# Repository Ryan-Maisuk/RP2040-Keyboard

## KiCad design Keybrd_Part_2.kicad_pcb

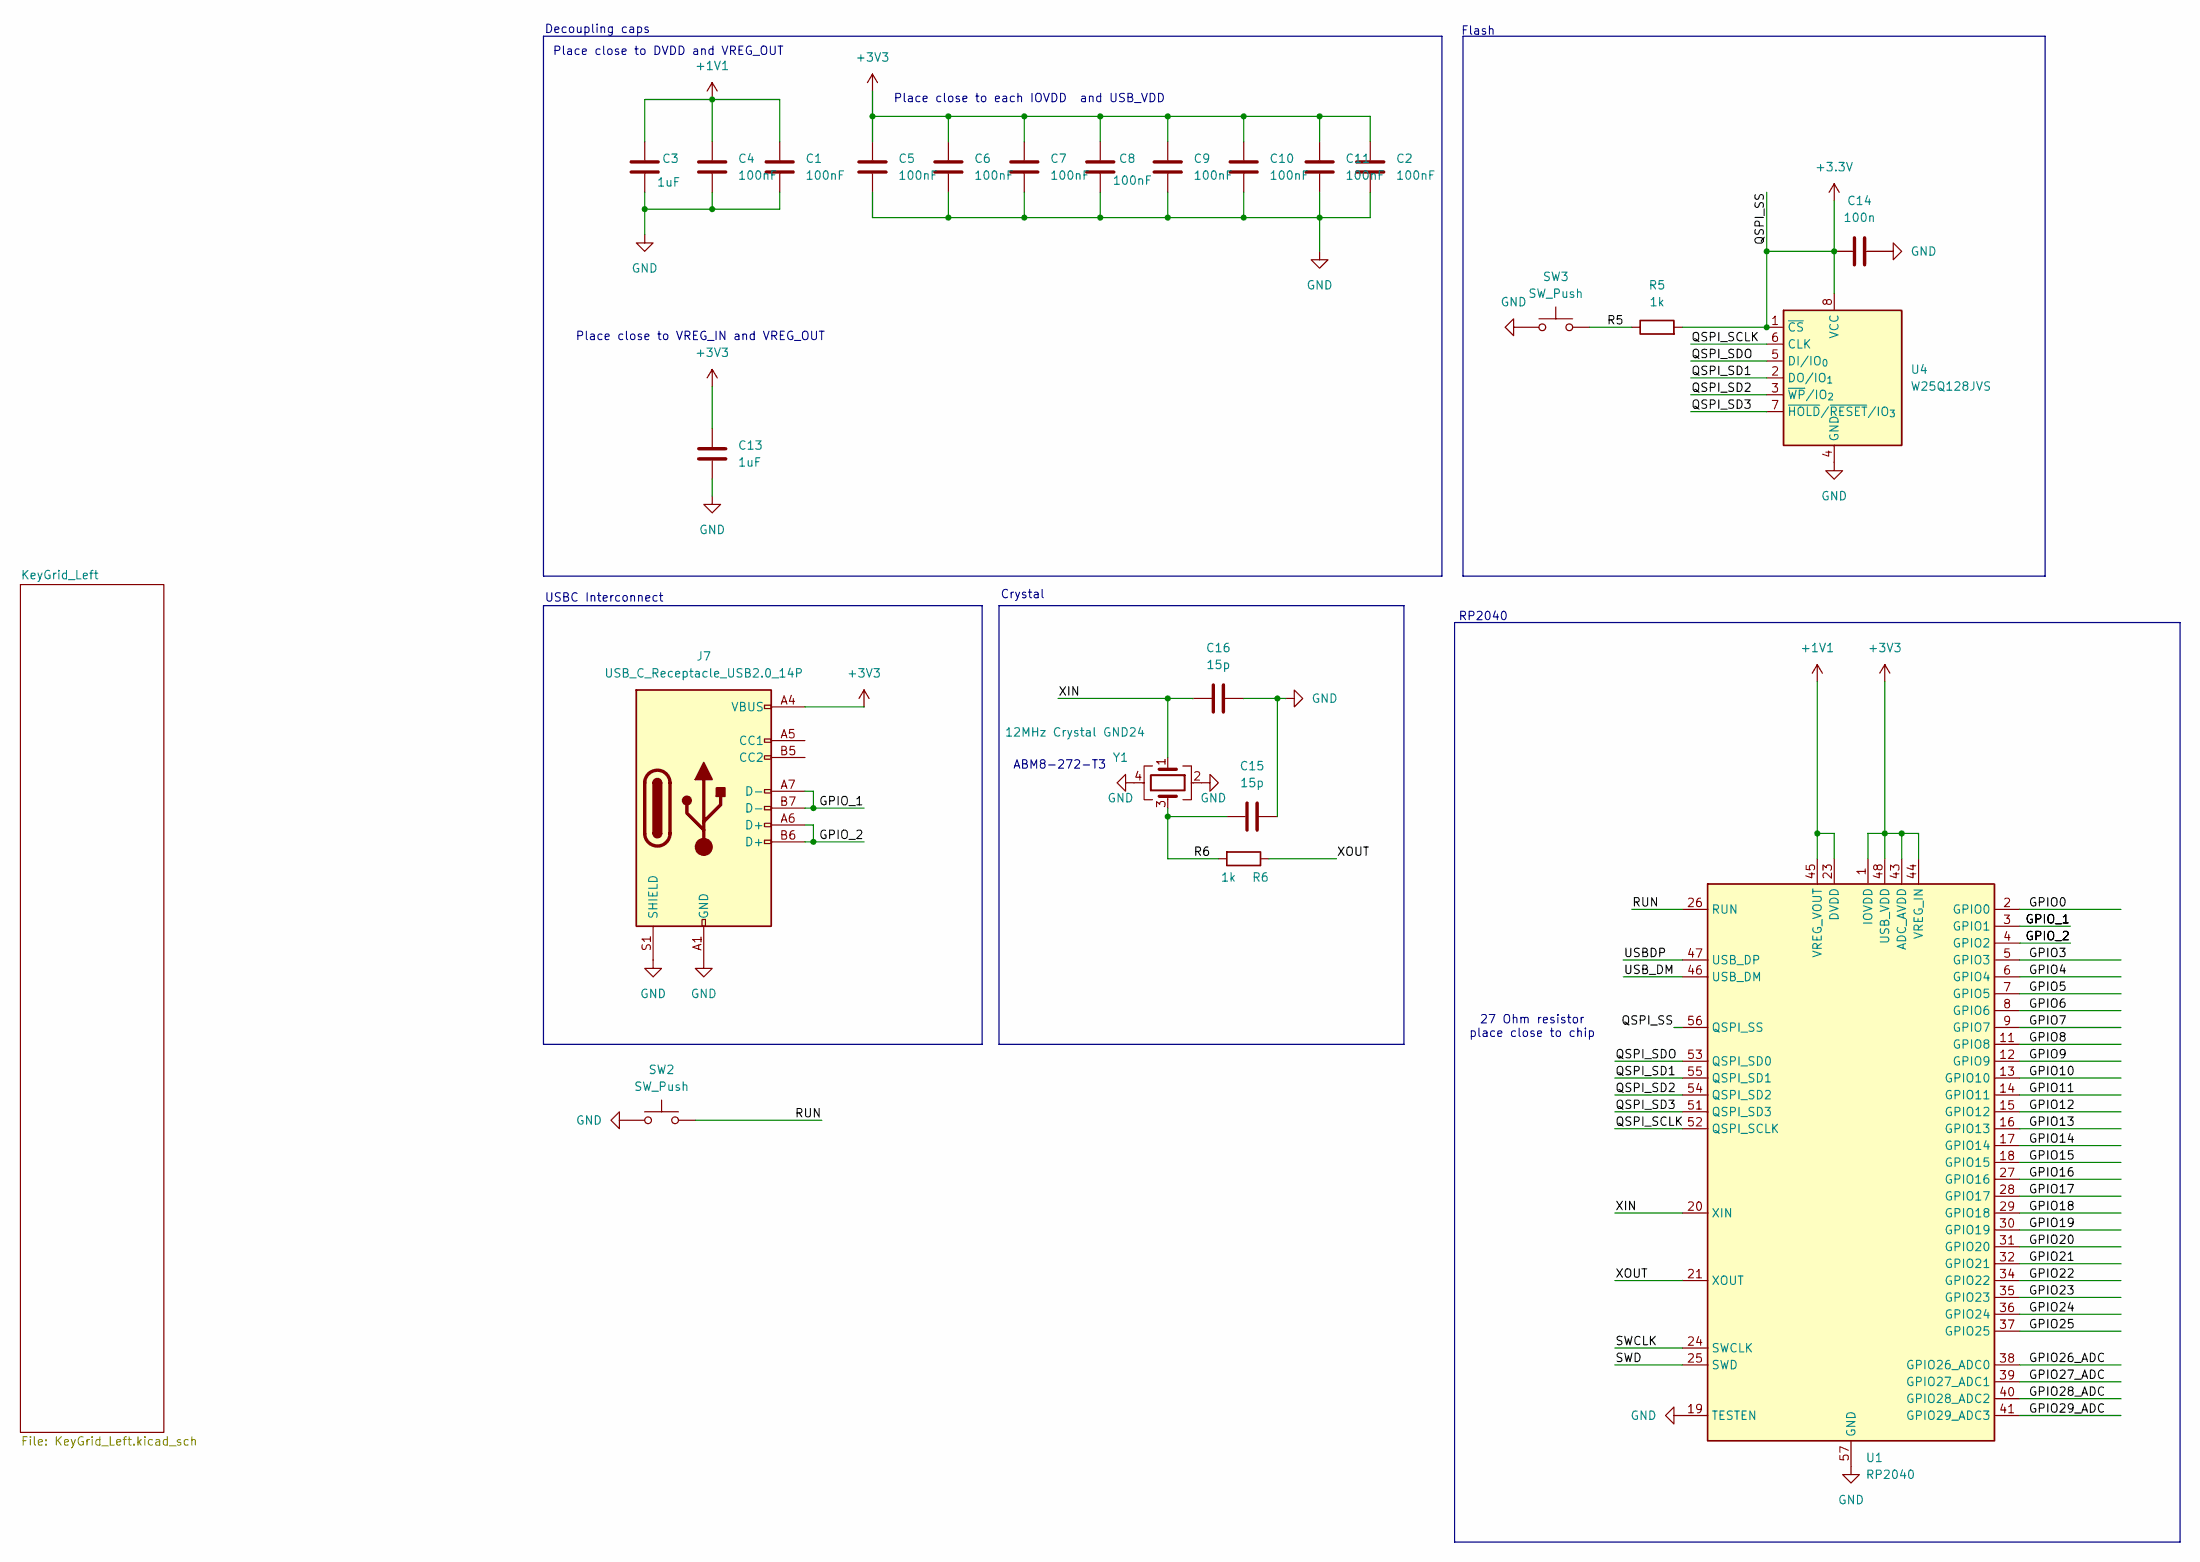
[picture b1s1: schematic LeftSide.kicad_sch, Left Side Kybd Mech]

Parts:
C1, C2, C4, C5, C6, C7, C8, C9, C10, C11: 100nF; C_0603_1608Metric_Pad1.08x0.95mm_HandSolder
C3, C13: 1uF; C_0603_1608Metric_Pad1.08x0.95mm_HandSolder
C14: 100n; C_0603_1608Metric_Pad1.08x0.95mm_HandSolder
C15, C16: 15p; C_0603_1608Metric_Pad1.08x0.95mm_HandSolder
J7: USB_C_Receptacle_USB2.0_14P; USB_C_Receptacle_Amphenol_12401548E4-2A
R5, R6: 1k; R_0603_1608Metric_Pad0.98x0.95mm_HandSolder
SW2, SW3: SW_Push; SW_PTS636_SM43J_SMTR_LFS
U1: RP2040; QFN-56-1EP_7x7mm_P0.4mm_EP3.2x3.2mm
U4: W25Q128JVS; SOIC-8_5.3x5.3mm_P1.27mm
Y1: 12MHz Crystal GND24; Crystal_SMD_3225-4Pin_3.2x2.5mm

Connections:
+1V1: C1.1, C3.1, C4.1, U1.23 (DVDD), U1.45 (VREG_VOUT), U1.50 (DVDD); also elsewhere on the board
+3.3V: C14.1, R5.2, U1.56 (QSPI_SS), U4.1 (~CS), U4.8 (VCC); also elsewhere on the board
+3V3: C2.1, C5.1, C6.1, C7.1, C8.2, C9.1, C10.1, C11.1, C13.1, J7.A4 (VBUS), J7.A9 (VBUS), J7.B4 (VBUS), J7.B9 (VBUS), U1.1 (IOVDD), U1.10 (IOVDD), U1.22 (IOVDD), U1.33 (IOVDD), U1.42 (IOVDD), U1.43 (ADC_AVDD), U1.44 (VREG_IN), U1.48 (USB_VDD), U1.49 (IOVDD); also elsewhere on the board
/LeftSide/GPIO0: U1.2 (GPIO0)
/LeftSide/GPIO3: U1.5 (GPIO3)
/LeftSide/GPIO4: U1.6 (GPIO4)
/LeftSide/GPIO5: U1.7 (GPIO5)
/LeftSide/GPIO6: U1.8 (GPIO6)
/LeftSide/GPIO7: U1.9 (GPIO7)
/LeftSide/GPIO8: U1.11 (GPIO8)
/LeftSide/GPIO9: U1.12 (GPIO9)
/LeftSide/GPIO10: U1.13 (GPIO10)
/LeftSide/GPIO11: U1.14 (GPIO11)
/LeftSide/GPIO12: U1.15 (GPIO12)
/LeftSide/GPIO13: U1.16 (GPIO13)
/LeftSide/GPIO14: U1.17 (GPIO14)
/LeftSide/GPIO15: U1.18 (GPIO15)
/LeftSide/GPIO16: U1.27 (GPIO16)
/LeftSide/GPIO17: U1.28 (GPIO17)
/LeftSide/GPIO18: U1.29 (GPIO18)
/LeftSide/GPIO19: U1.30 (GPIO19)
/LeftSide/GPIO20: U1.31 (GPIO20)
/LeftSide/GPIO21: U1.32 (GPIO21)
/LeftSide/GPIO22: U1.34 (GPIO22)
/LeftSide/GPIO23: U1.35 (GPIO23)
/LeftSide/GPIO24: U1.36 (GPIO24)
/LeftSide/GPIO25: U1.37 (GPIO25)
/LeftSide/GPIO26_ADC: U1.38 (GPIO26_ADC0)
/LeftSide/GPIO27_ADC: U1.39 (GPIO27_ADC1)
/LeftSide/GPIO28_ADC: U1.40 (GPIO28_ADC2)
/LeftSide/GPIO29_ADC: U1.41 (GPIO29_ADC3)
/LeftSide/GPIO_1: J7.A7 (D-), J7.B7 (D-), U1.3 (GPIO1)
/LeftSide/GPIO_2: J7.A6 (D+), J7.B6 (D+), U1.4 (GPIO2)
/LeftSide/QSPI_SCLK: U1.52 (QSPI_SCLK), U4.6 (CLK)
/LeftSide/QSPI_SD1: U1.55 (QSPI_SD1), U4.2 (DO/IO_{1})
/LeftSide/QSPI_SD2: U1.54 (QSPI_SD2), U4.3 (~WP/IO_{2})
/LeftSide/QSPI_SD3: U1.51 (QSPI_SD3), U4.7 (~HOLD/~RESET/IO_{3})
/LeftSide/QSPI_SDO: U1.53 (QSPI_SD0), U4.5 (DI/IO_{0})
/LeftSide/R5: R5.1, SW3.2
/LeftSide/R6: C15.1, R6.2, Y1.3
/LeftSide/RUN: SW2.2, U1.26 (RUN)
/LeftSide/SWCLK: U1.24 (SWCLK)
/LeftSide/SWD: U1.25 (SWD)
/LeftSide/USBDP: U1.47 (USB_DP)
/LeftSide/USB_DM: U1.46 (USB_DM)
/LeftSide/XIN: C16.1, U1.20 (XIN), Y1.1
/LeftSide/XOUT: R6.1, U1.21 (XOUT)
GND: C1.2, C2.2, C3.2, C4.2, C5.2, C6.2, C7.2, C8.1, C9.2, C10.2, C11.2, C13.2, C14.2, C15.2, C16.2, J7.A1 (GND), J7.A12 (GND), J7.B1 (GND), J7.B12 (GND), J7.S1 (SHIELD), SW2.1, SW3.1, U1.19 (TESTEN), U1.57 (GND), U4.4 (GND), Y1.2, Y1.4; also elsewhere on the board

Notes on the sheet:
RP2040
Place close to each IOVDD and USB_VDD
USBC Interconnect
27 Ohm resistor place close to chip
Decoupling caps
Flash
Place close to DVDD and VREG_OUT
ABM8-272-T3
Crystal
Place close to VREG_IN and VREG_OUT

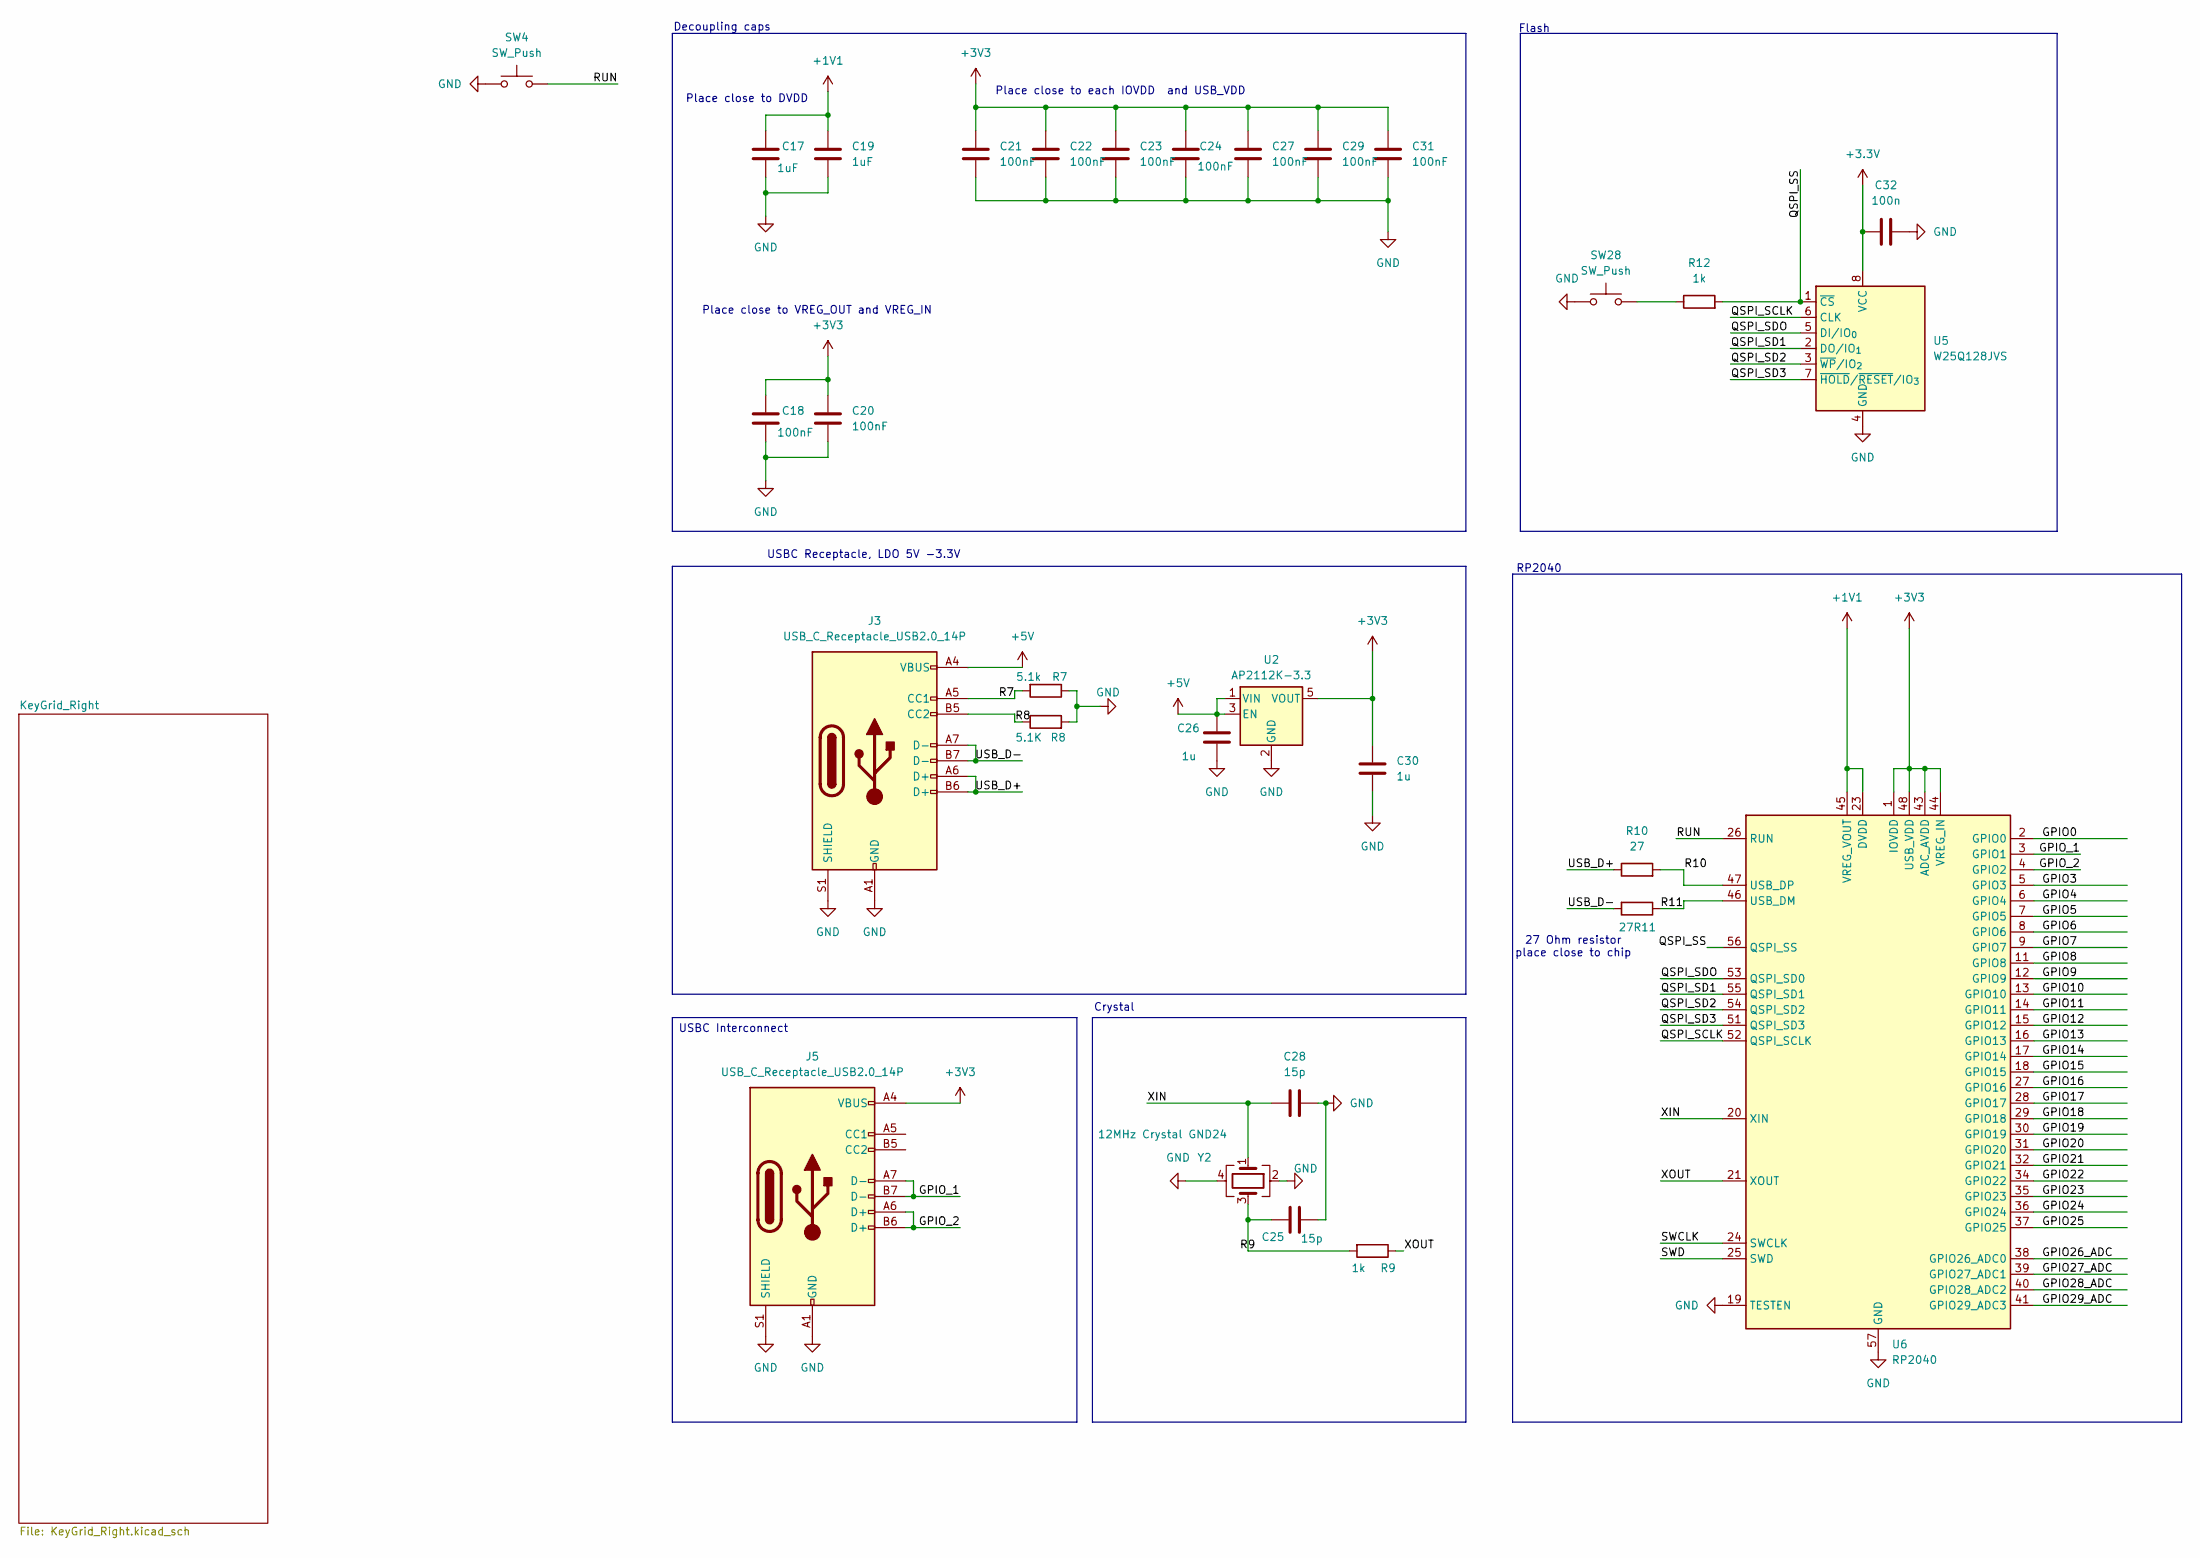
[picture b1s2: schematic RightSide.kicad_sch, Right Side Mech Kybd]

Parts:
C17, C19: 1uF; C_0603_1608Metric_Pad1.08x0.95mm_HandSolder
C18, C20, C21, C22, C23, C24, C27, C29, C31: 100nF; C_0603_1608Metric_Pad1.08x0.95mm_HandSolder
C25, C28: 15p; C_0603_1608Metric_Pad1.08x0.95mm_HandSolder
C26, C30: 1u; C_0603_1608Metric_Pad1.08x0.95mm_HandSolder
C32: 100n; C_0603_1608Metric_Pad1.08x0.95mm_HandSolder
J3, J5: USB_C_Receptacle_USB2.0_14P; USB_C_Receptacle_Amphenol_12401548E4-2A
R7: 5.1k; R_0603_1608Metric_Pad0.98x0.95mm_HandSolder
R8: 5.1K; R_0603_1608Metric_Pad0.98x0.95mm_HandSolder
R9, R12: 1k; R_0603_1608Metric_Pad0.98x0.95mm_HandSolder
R10, R11: 27; R_0603_1608Metric_Pad0.98x0.95mm_HandSolder
SW4, SW28: SW_Push; SW_PTS636_SM43J_SMTR_LFS
U2: AP2112K-3.3; SOT-23-5
U5: W25Q128JVS; SOIC-8_5.3x5.3mm_P1.27mm
U6: RP2040; QFN-56-1EP_7x7mm_P0.4mm_EP3.2x3.2mm
Y2: 12MHz Crystal GND24; Crystal_SMD_3225-4Pin_3.2x2.5mm

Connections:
+1V1: C17.1, C19.1, U6.23 (DVDD), U6.45 (VREG_VOUT), U6.50 (DVDD); also elsewhere on the board
+3.3V: C32.1, U5.8 (VCC); also elsewhere on the board
+3V3: C18.1, C20.1, C21.1, C22.1, C23.1, C24.2, C27.1, C29.1, C30.1, C31.1, J5.A4 (VBUS), J5.A9 (VBUS), J5.B4 (VBUS), J5.B9 (VBUS), U2.5 (VOUT), U6.1 (IOVDD), U6.10 (IOVDD), U6.22 (IOVDD), U6.33 (IOVDD), U6.42 (IOVDD), U6.43 (ADC_AVDD), U6.44 (VREG_IN), U6.48 (USB_VDD), U6.49 (IOVDD); also elsewhere on the board
+5V: C26.1, J3.A4 (VBUS), J3.A9 (VBUS), J3.B4 (VBUS), J3.B9 (VBUS), U2.1 (VIN), U2.3 (EN)
/RightSide/GPIO0: U6.2 (GPIO0)
/RightSide/GPIO3: U6.5 (GPIO3)
/RightSide/GPIO4: U6.6 (GPIO4)
/RightSide/GPIO5: U6.7 (GPIO5)
/RightSide/GPIO6: U6.8 (GPIO6)
/RightSide/GPIO7: U6.9 (GPIO7)
/RightSide/GPIO8: U6.11 (GPIO8)
/RightSide/GPIO9: U6.12 (GPIO9)
/RightSide/GPIO10: U6.13 (GPIO10)
/RightSide/GPIO11: U6.14 (GPIO11)
/RightSide/GPIO12: U6.15 (GPIO12)
/RightSide/GPIO13: U6.16 (GPIO13)
/RightSide/GPIO14: U6.17 (GPIO14)
/RightSide/GPIO15: U6.18 (GPIO15)
/RightSide/GPIO16: U6.27 (GPIO16)
/RightSide/GPIO17: U6.28 (GPIO17)
/RightSide/GPIO18: U6.29 (GPIO18)
/RightSide/GPIO19: U6.30 (GPIO19)
/RightSide/GPIO20: U6.31 (GPIO20)
/RightSide/GPIO21: U6.32 (GPIO21)
/RightSide/GPIO22: U6.34 (GPIO22)
/RightSide/GPIO23: U6.35 (GPIO23)
/RightSide/GPIO24: U6.36 (GPIO24)
/RightSide/GPIO25: U6.37 (GPIO25)
/RightSide/GPIO26_ADC: U6.38 (GPIO26_ADC0)
/RightSide/GPIO27_ADC: U6.39 (GPIO27_ADC1)
/RightSide/GPIO28_ADC: U6.40 (GPIO28_ADC2)
/RightSide/GPIO29_ADC: U6.41 (GPIO29_ADC3)
/RightSide/GPIO_1: J5.A7 (D-), J5.B7 (D-), U6.3 (GPIO1)
/RightSide/GPIO_2: J5.A6 (D+), J5.B6 (D+), U6.4 (GPIO2)
/RightSide/QSPI_SCLK: U5.6 (CLK), U6.52 (QSPI_SCLK)
/RightSide/QSPI_SD1: U5.2 (DO/IO_{1}), U6.55 (QSPI_SD1)
/RightSide/QSPI_SD2: U5.3 (~WP/IO_{2}), U6.54 (QSPI_SD2)
/RightSide/QSPI_SD3: U5.7 (~HOLD/~RESET/IO_{3}), U6.51 (QSPI_SD3)
/RightSide/QSPI_SDO: U5.5 (DI/IO_{0}), U6.53 (QSPI_SD0)
/RightSide/QSPI_SS: R12.2, U5.1 (~CS), U6.56 (QSPI_SS)
/RightSide/R7: J3.A5 (CC1), R7.2
/RightSide/R8: J3.B5 (CC2), R8.1
/RightSide/R9: C25.1, R9.2, Y2.3
/RightSide/R10: R10.2, U6.47 (USB_DP)
/RightSide/R11: R11.1, U6.46 (USB_DM)
/RightSide/RUN: SW4.2, U6.26 (RUN)
/RightSide/SWCLK: U6.24 (SWCLK)
/RightSide/SWD: U6.25 (SWD)
/RightSide/USB_D+: J3.A6 (D+), J3.B6 (D+), R10.1
/RightSide/USB_D-: J3.A7 (D-), J3.B7 (D-), R11.2
/RightSide/XIN: C28.1, U6.20 (XIN), Y2.1
/RightSide/XOUT: R9.1, U6.21 (XOUT)
GND: C17.2, C18.2, C19.2, C20.2, C21.2, C22.2, C23.2, C24.1, C25.2, C26.2, C27.2, C28.2, C29.2, C30.2, C31.2, C32.2, J3.A1 (GND), J3.A12 (GND), J3.B1 (GND), J3.B12 (GND), J3.S1 (SHIELD), J5.A1 (GND), J5.A12 (GND), J5.B1 (GND), J5.B12 (GND), J5.S1 (SHIELD), R7.1, R8.2, SW4.1, SW28.1, U2.2 (GND), U5.4 (GND), U6.19 (TESTEN), U6.57 (GND), Y2.2, Y2.4; also elsewhere on the board
unnamed: R12.1, SW28.2

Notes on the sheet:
RP2040
Flash
Decoupling caps
USBC Receptacle, LDO 5V -3.3V
Crystal
27 Ohm resistor place close to chip
Place close to each IOVDD and USB_VDD
Place close to VREG_OUT and VREG_IN
Place close to DVDD
USBC Interconnect

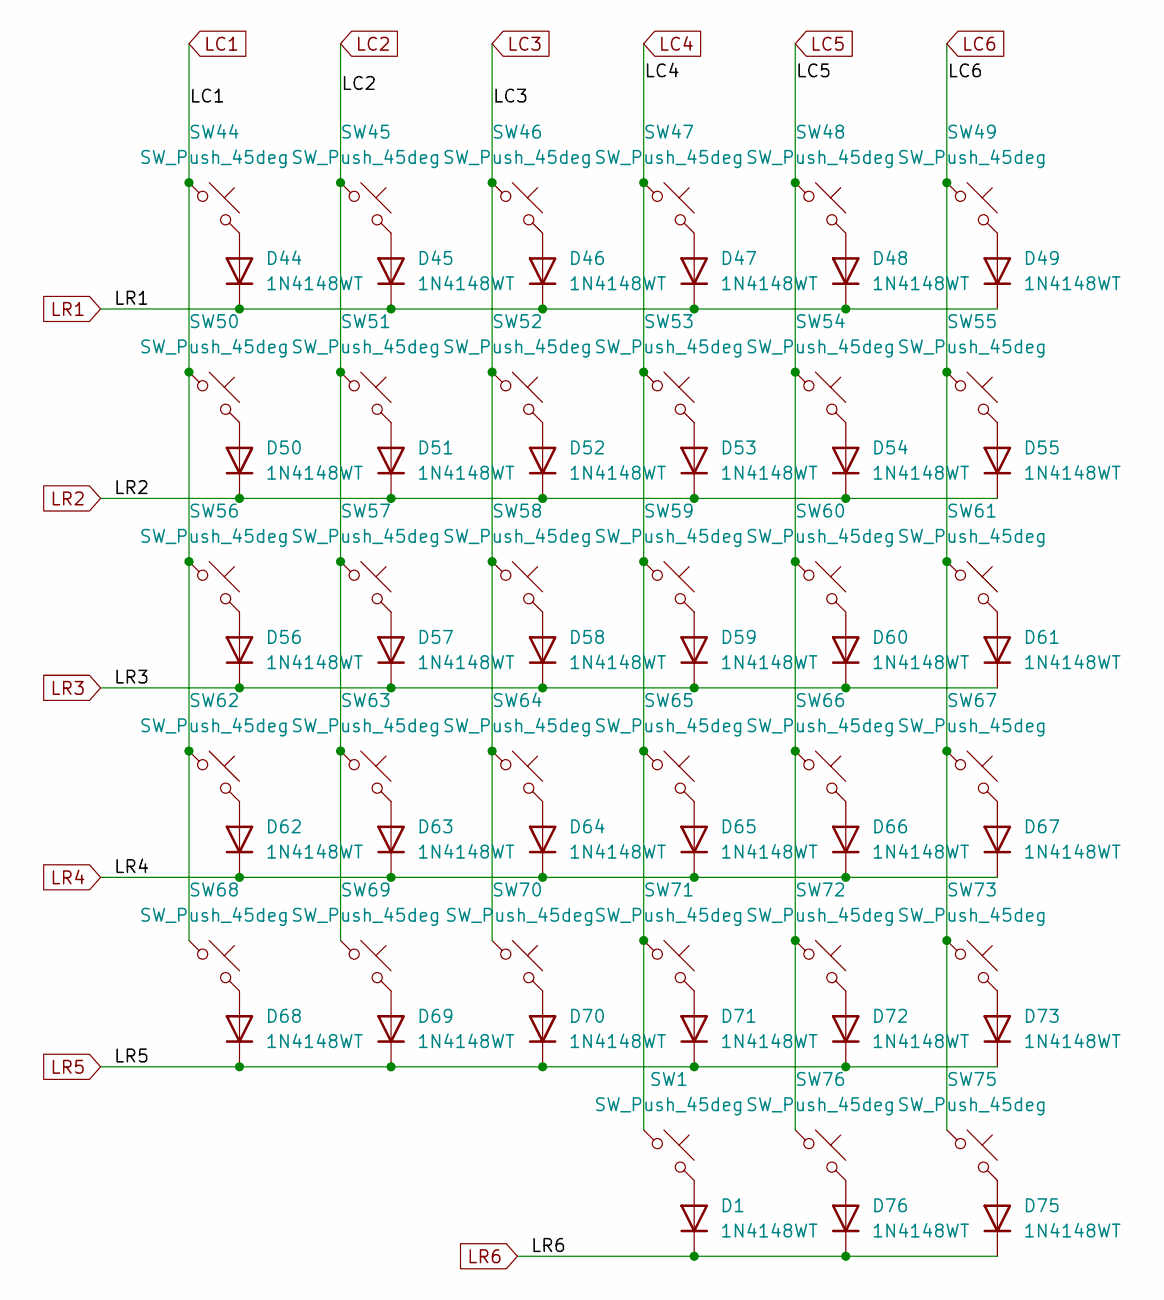
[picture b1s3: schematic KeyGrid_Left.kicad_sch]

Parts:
D1, D44, D45, D46, D47, D48, D49, D50, D51, D52, D53, D54, D55, D56, D57, D58, D59, D60, D61, D62, D63, D64, D65, D66, D67, D68, D69, D70, D71, D72, D73, D75, D76: 1N4148WT; D_SOD-123
SW1, SW44, SW45, SW46, SW47, SW48, SW49, SW50, SW51, SW52, SW53, SW54, SW55, SW56, SW57, SW58, SW59, SW60, SW61, SW62, SW63, SW64, SW65, SW66, SW67, SW68, SW69, SW70, SW71, SW72, SW73, SW75, SW76: SW_Push_45deg; SW_Cherry_MX_1.00u_PCB

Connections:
LC1: SW44.1, SW50.1, SW56.1, SW62.1, SW68.1
LC2: SW45.1, SW51.1, SW57.1, SW63.1, SW69.1
LC3: SW46.1, SW52.1, SW58.1, SW64.1, SW70.1
LC4: SW1.1, SW47.1, SW53.1, SW59.1, SW65.1, SW71.1
LC5: SW48.1, SW54.1, SW60.1, SW66.1, SW72.1, SW76.1
LC6: SW49.1, SW55.1, SW61.1, SW67.1, SW73.1, SW75.1
LR1: D44.1 (K), D45.1 (K), D46.1 (K), D47.1 (K), D48.1 (K), D49.1 (K)
LR2: D50.1 (K), D51.1 (K), D52.1 (K), D53.1 (K), D54.1 (K), D55.1 (K)
LR3: D56.1 (K), D57.1 (K), D58.1 (K), D59.1 (K), D60.1 (K), D61.1 (K)
LR4: D62.1 (K), D63.1 (K), D64.1 (K), D65.1 (K), D66.1 (K), D67.1 (K)
LR5: D68.1 (K), D69.1 (K), D70.1 (K), D71.1 (K), D72.1 (K), D73.1 (K)
LR6: D1.1 (K), D75.1 (K), D76.1 (K)
unnamed: D1.2 (A), SW1.2
unnamed: D44.2 (A), SW44.2
unnamed: D45.2 (A), SW45.2
unnamed: D46.2 (A), SW46.2
unnamed: D47.2 (A), SW47.2
unnamed: D48.2 (A), SW48.2
unnamed: D49.2 (A), SW49.2
unnamed: D50.2 (A), SW50.2
unnamed: D51.2 (A), SW51.2
unnamed: D52.2 (A), SW52.2
unnamed: D53.2 (A), SW53.2
unnamed: D54.2 (A), SW54.2
unnamed: D55.2 (A), SW55.2
unnamed: D56.2 (A), SW56.2
unnamed: D57.2 (A), SW57.2
unnamed: D58.2 (A), SW58.2
unnamed: D59.2 (A), SW59.2
unnamed: D60.2 (A), SW60.2
unnamed: D61.2 (A), SW61.2
unnamed: D62.2 (A), SW62.2
unnamed: D63.2 (A), SW63.2
unnamed: D64.2 (A), SW64.2
unnamed: D65.2 (A), SW65.2
unnamed: D66.2 (A), SW66.2
unnamed: D67.2 (A), SW67.2
unnamed: D68.2 (A), SW68.2
unnamed: D69.2 (A), SW69.2
unnamed: D70.2 (A), SW70.2
unnamed: D71.2 (A), SW71.2
unnamed: D72.2 (A), SW72.2
unnamed: D73.2 (A), SW73.2
unnamed: D75.2 (A), SW75.2
unnamed: D76.2 (A), SW76.2

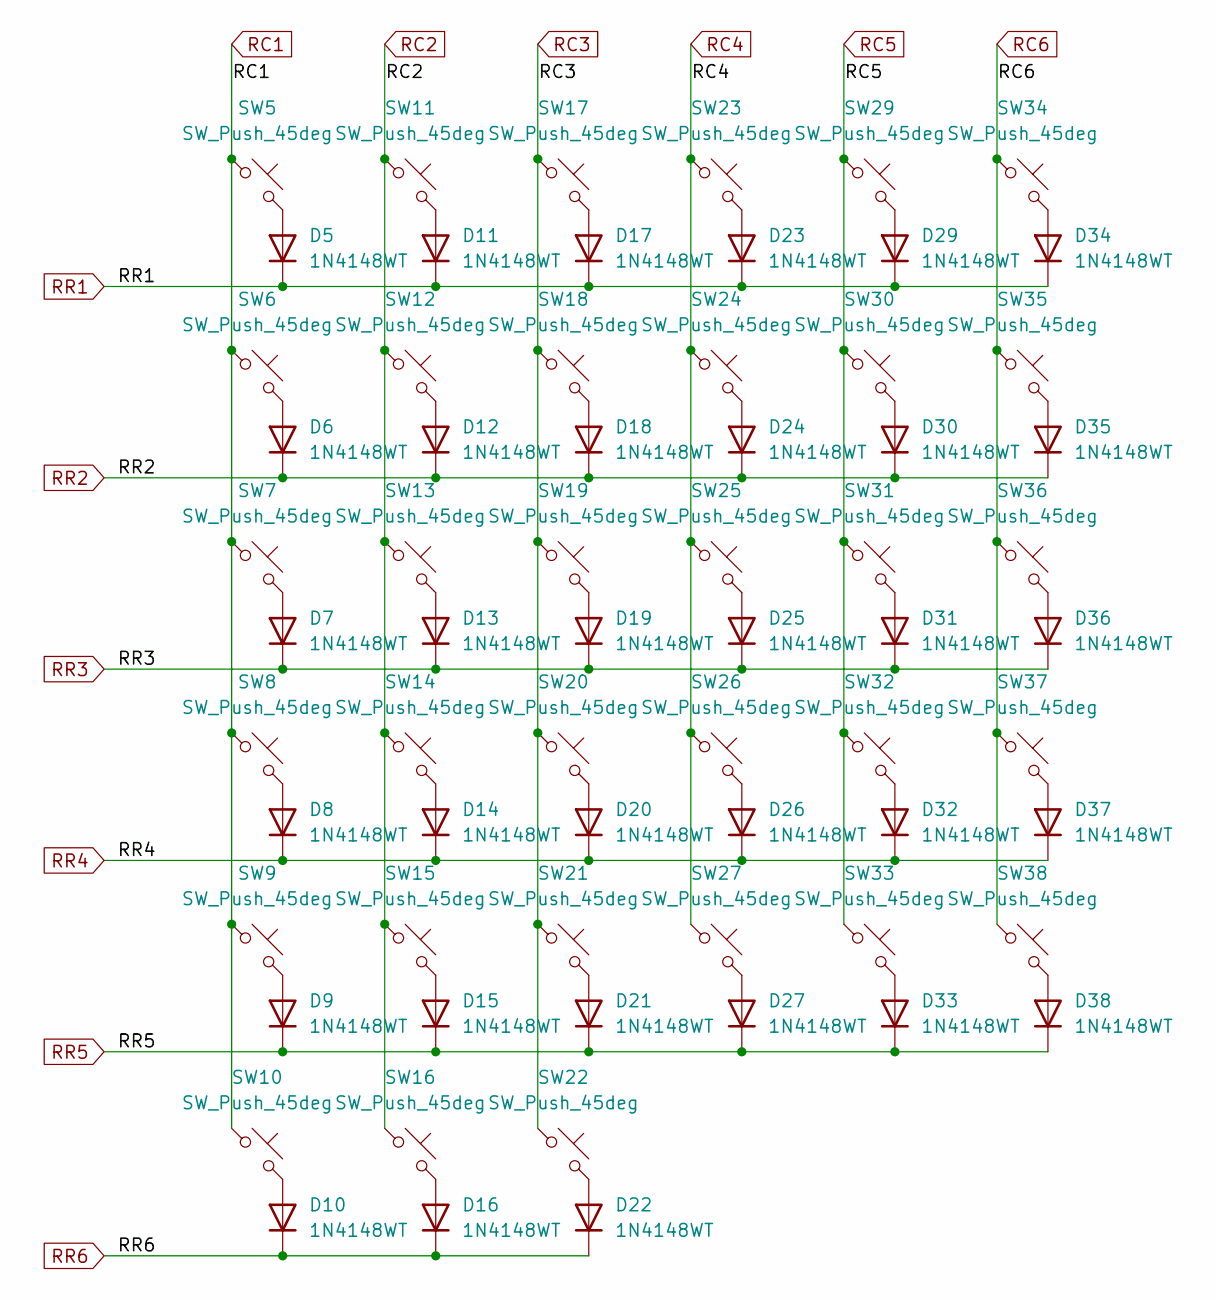
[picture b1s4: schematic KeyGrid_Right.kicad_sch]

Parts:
D5, D6, D7, D8, D9, D10, D11, D12, D13, D14, D15, D16, D17, D18, D19, D20, D21, D22, D23, D24, D25, D26, D27, D29, D30, D31, D32, D33, D34, D35, D36, D37, D38: 1N4148WT; D_SOD-123
SW5, SW6, SW7, SW8, SW9, SW10, SW11, SW12, SW13, SW14, SW15, SW16, SW17, SW18, SW19, SW20, SW21, SW22, SW23, SW24, SW25, SW26, SW27, SW29, SW30, SW31, SW32, SW33, SW34, SW35, SW36, SW37, SW38: SW_Push_45deg; SW_Cherry_MX_1.00u_PCB

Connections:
unnamed: D5.2 (A), SW5.2
unnamed: D6.2 (A), SW6.2
unnamed: D7.2 (A), SW7.2
unnamed: D8.2 (A), SW8.2
unnamed: D9.2 (A), SW9.2
unnamed: D10.2 (A), SW10.2
unnamed: D11.2 (A), SW11.2
unnamed: D12.2 (A), SW12.2
unnamed: D13.2 (A), SW13.2
unnamed: D14.2 (A), SW14.2
unnamed: D15.2 (A), SW15.2
unnamed: D16.2 (A), SW16.2
unnamed: D17.2 (A), SW17.2
unnamed: D18.2 (A), SW18.2
unnamed: D19.2 (A), SW19.2
unnamed: D20.2 (A), SW20.2
unnamed: D21.2 (A), SW21.2
unnamed: D22.2 (A), SW22.2
unnamed: D23.2 (A), SW23.2
unnamed: D24.2 (A), SW24.2
unnamed: D25.2 (A), SW25.2
unnamed: D26.2 (A), SW26.2
unnamed: D27.2 (A), SW27.2
unnamed: D29.2 (A), SW29.2
unnamed: D30.2 (A), SW30.2
unnamed: D31.2 (A), SW31.2
unnamed: D32.2 (A), SW32.2
unnamed: D33.2 (A), SW33.2
unnamed: D34.2 (A), SW34.2
unnamed: D35.2 (A), SW35.2
unnamed: D36.2 (A), SW36.2
unnamed: D37.2 (A), SW37.2
unnamed: D38.2 (A), SW38.2
RC1: SW5.1, SW6.1, SW7.1, SW8.1, SW9.1, SW10.1
RC2: SW11.1, SW12.1, SW13.1, SW14.1, SW15.1, SW16.1
RC3: SW17.1, SW18.1, SW19.1, SW20.1, SW21.1, SW22.1
RC4: SW23.1, SW24.1, SW25.1, SW26.1, SW27.1
RC5: SW29.1, SW30.1, SW31.1, SW32.1, SW33.1
RC6: SW34.1, SW35.1, SW36.1, SW37.1, SW38.1
RR1: D5.1 (K), D11.1 (K), D17.1 (K), D23.1 (K), D29.1 (K), D34.1 (K)
RR2: D6.1 (K), D12.1 (K), D18.1 (K), D24.1 (K), D30.1 (K), D35.1 (K)
RR3: D7.1 (K), D13.1 (K), D19.1 (K), D25.1 (K), D31.1 (K), D36.1 (K)
RR4: D8.1 (K), D14.1 (K), D20.1 (K), D26.1 (K), D32.1 (K), D37.1 (K)
RR5: D9.1 (K), D15.1 (K), D21.1 (K), D27.1 (K), D33.1 (K), D38.1 (K)
RR6: D10.1 (K), D16.1 (K), D22.1 (K)

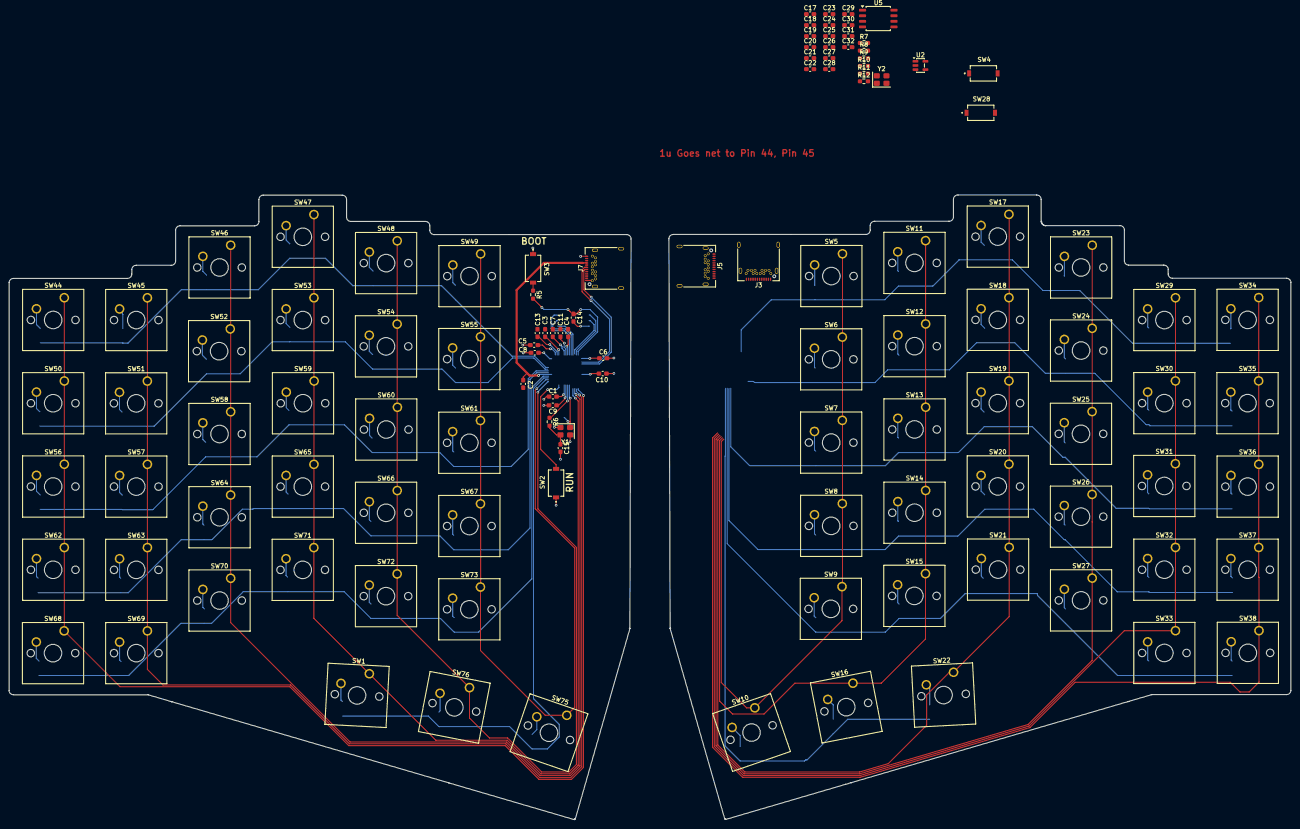
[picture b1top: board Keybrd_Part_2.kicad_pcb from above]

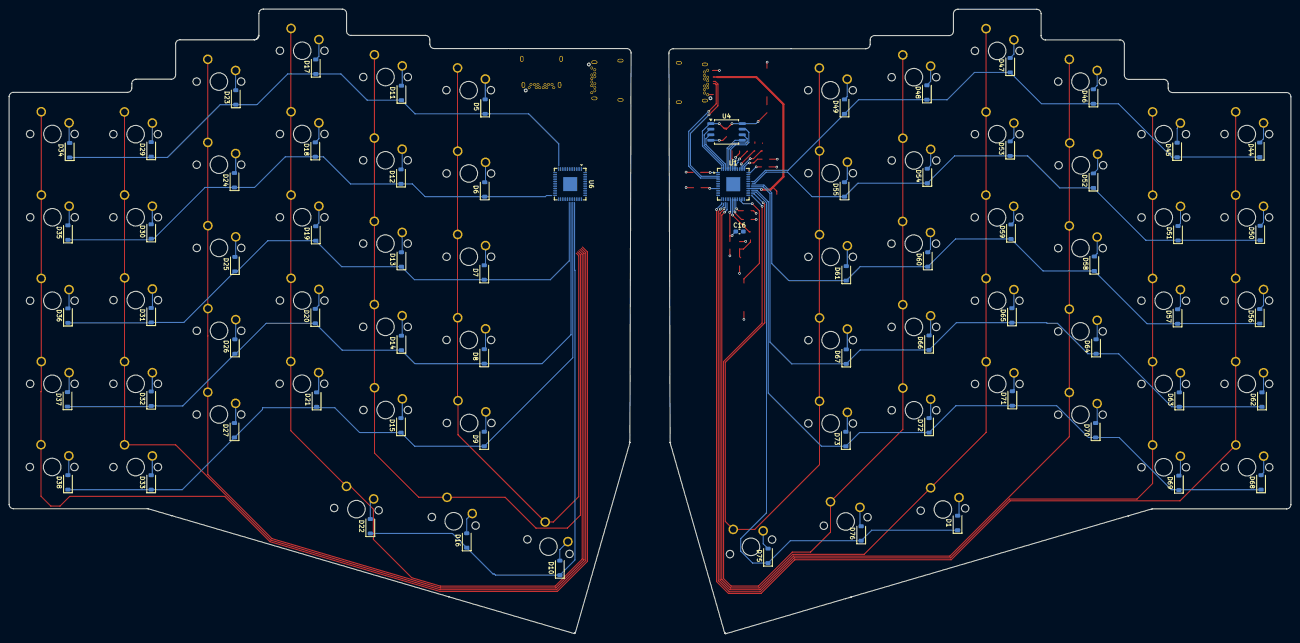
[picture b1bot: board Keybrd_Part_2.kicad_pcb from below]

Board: 2 copper layers, 292.5 x 142.5 mm, 185 parts (70 on the bottom side), 126 nets.
